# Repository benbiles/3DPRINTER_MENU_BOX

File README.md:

# 3DPRINTER-MENU-BOX

concept: a low cost 3d printer AC fan controller and power switcher for enclosure tempterture regulation and saftey power shutdown 

mainboard uses ESP32 DevKit V1 with Arduino code
screen menu with 4 tactile buttons
1 x OLED screen
2 x DS18B20 Temp sensor channels
2 channels Variable AC 110v / 240v for fan speed control
2 channels 110V / 240V AC solid state relay SSR for shutdown on timer or over temp safety shutdown.

future Mobile APP alarm / notifications / warnings using MIT app inventor.

https://hackaday.io/project/190382-3dprinter-menu-box

current status:
basic menu , oled screen and button with debounce are working.
1 channel temp sensor is working

testing to do soon..
AC fan controller boards and enclosure temp regulation.
extracting the air cools the enclosure too much ?
install a heppa filter and recycle air back into enclosure with fan 1 and extract air with other
when enclosure becomes over temptetur with fan 2 ? 
test power shutdown in case of over temp.

to do later..
install smoke detector for emergency power down.
web cam image minitoring even if just stills taken at intervals.

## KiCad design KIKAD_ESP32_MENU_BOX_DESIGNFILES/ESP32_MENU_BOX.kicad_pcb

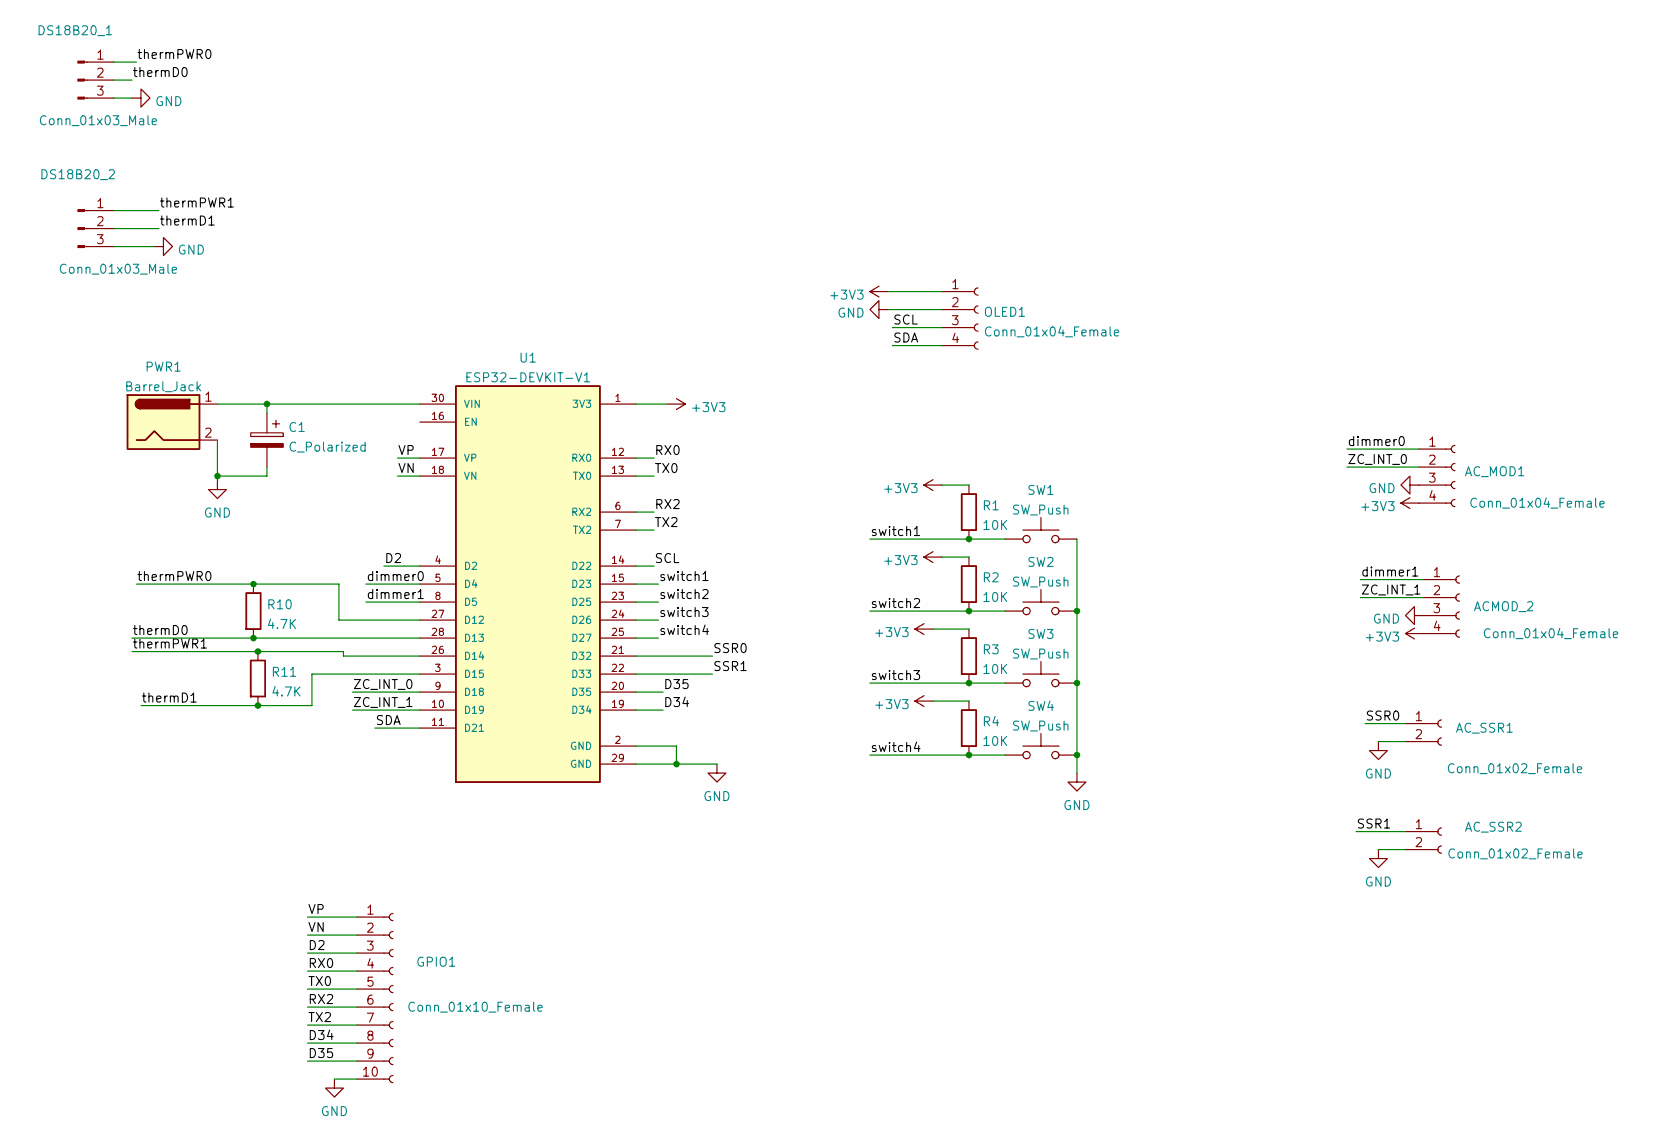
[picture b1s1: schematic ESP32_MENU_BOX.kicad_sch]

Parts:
ACMOD_2: Conn_01x04_Female; PinSocket_1x04_P2.54mm_Vertical
AC_MOD1: Conn_01x04_Female; PinSocket_1x04_P2.54mm_Vertical
AC_SSR1, AC_SSR2: Conn_01x02_Female; PinSocket_1x02_P2.54mm_Vertical
C1: C_Polarized; CP_Elec_8x5.4
DS18B20_1, DS18B20_2: Conn_01x03_Male; PinHeader_1x03_P2.54mm_Vertical
GPIO1: Conn_01x10_Female; PinSocket_1x10_P2.54mm_Vertical
OLED1: Conn_01x04_Female; PinHeader_1x04_P2.54mm_Vertical
PWR1: Barrel_Jack; BarrelJack_GCT_DCJ200-10-A_Horizontal
R1, R2, R3, R4: 10K; R_0603_1608Metric_Pad0.98x0.95mm_HandSolder
R10, R11: 4.7K; R_0603_1608Metric_Pad0.98x0.95mm_HandSolder
SW1, SW2, SW3, SW4: SW_Push; SW_SPST_EVQP2
U1: ESP32-DEVKIT-V1; MODULE_ESP32_DEVKIT_V1; PARTREV N/A

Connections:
+3V3: ACMOD_2.4, AC_MOD1.4, OLED1.1, R1.1, R2.1, R3.1, R4.1, U1.1 (3V3)
/D2: GPIO1.3, U1.4 (D2)
/D34: GPIO1.8, U1.19 (D34)
/D35: GPIO1.9, U1.20 (D35)
/RX0: GPIO1.4, U1.12 (RX0)
/RX2: GPIO1.6, U1.6 (RX2)
/SCL: OLED1.3, U1.14 (D22)
/SDA: OLED1.4, U1.11 (D21)
/SSR0: AC_SSR1.1, U1.21 (D32)
/SSR1: AC_SSR2.1, U1.22 (D33)
/TX0: GPIO1.5, U1.13 (TX0)
/TX2: GPIO1.7, U1.7 (TX2)
/VN: GPIO1.2, U1.18 (VN)
/VP: GPIO1.1, U1.17 (VP)
/ZC_INT_0: AC_MOD1.2, U1.9 (D18)
/ZC_INT_1: ACMOD_2.2, U1.10 (D19)
/dimmer0: AC_MOD1.1, U1.5 (D4)
/dimmer1: ACMOD_2.1, U1.8 (D5)
/switch1: R1.2, SW1.1, U1.15 (D23)
/switch2: R2.2, SW2.1, U1.23 (D25)
/switch3: R3.2, SW3.1, U1.24 (D26)
/switch4: R4.2, SW4.1, U1.25 (D27)
/thermD0: DS18B20_1.2, R10.2, U1.28 (D13)
/thermD1: DS18B20_2.2, R11.2, U1.3 (D15)
/thermPWR0: DS18B20_1.1, R10.1, U1.27 (D12)
/thermPWR1: DS18B20_2.1, R11.1, U1.26 (D14)
GND: ACMOD_2.3, AC_MOD1.3, AC_SSR1.2, AC_SSR2.2, C1.2, DS18B20_1.3, DS18B20_2.3, GPIO1.10, OLED1.2, PWR1.2, SW1.2, SW2.2, SW3.2, SW4.2, U1.2 (GND), U1.29 (GND)
unnamed: C1.1, PWR1.1, U1.30 (VIN)

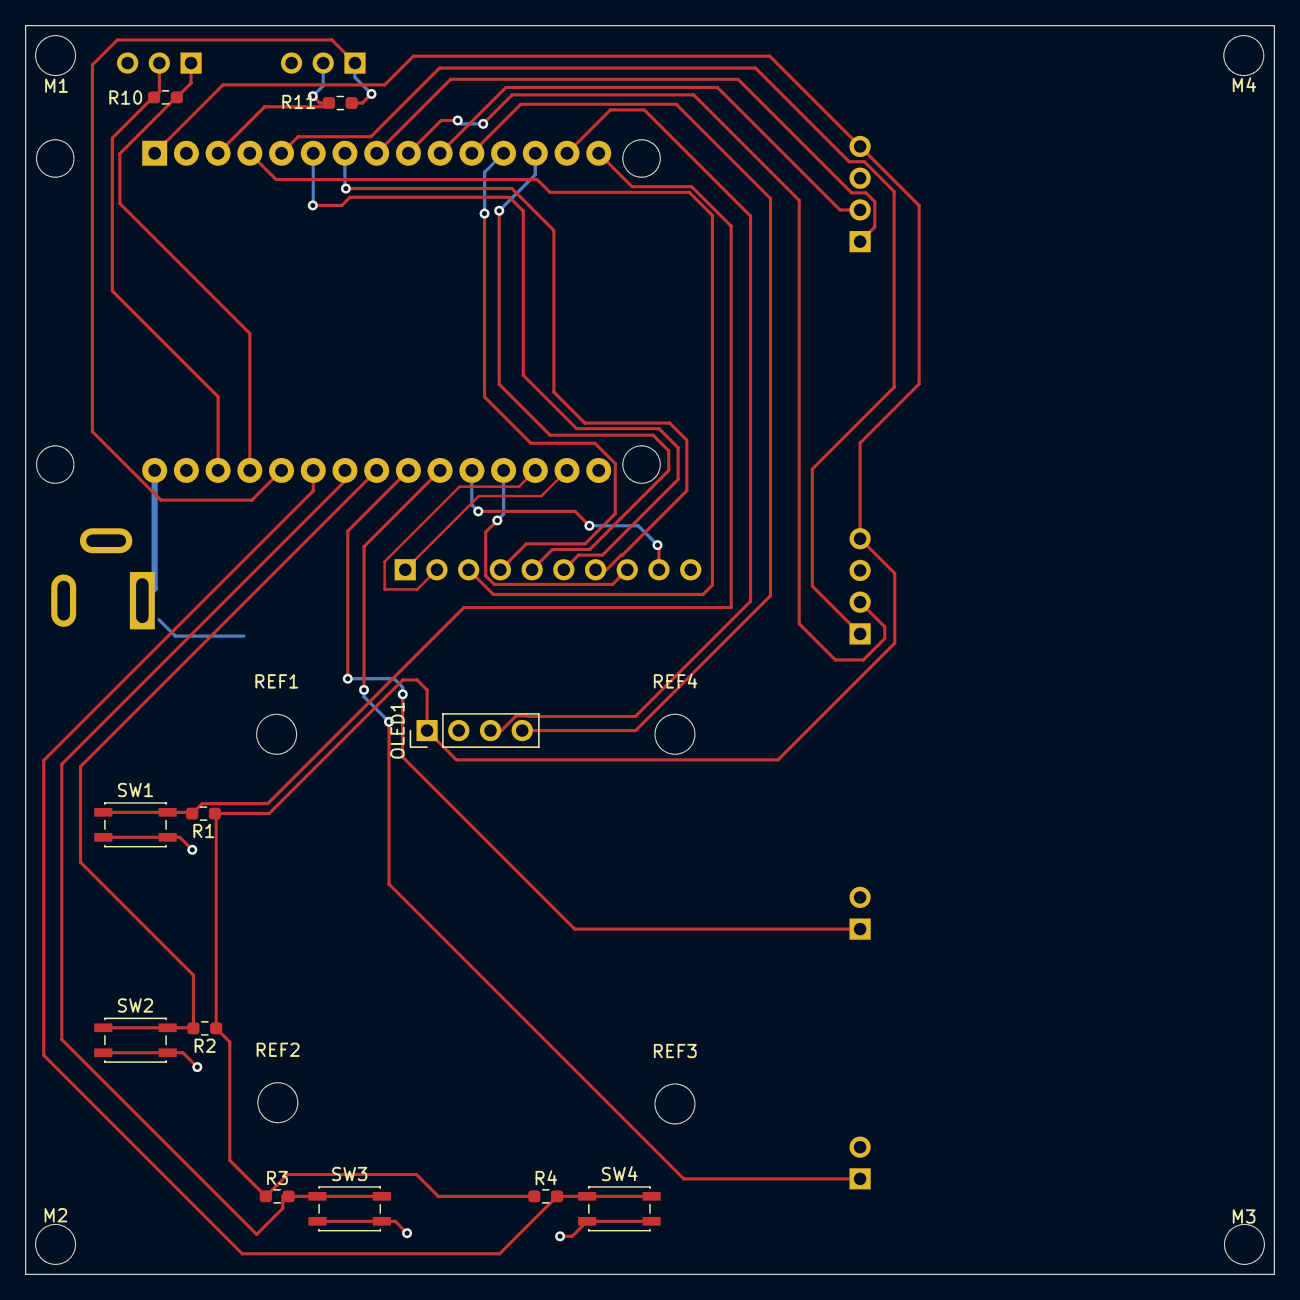
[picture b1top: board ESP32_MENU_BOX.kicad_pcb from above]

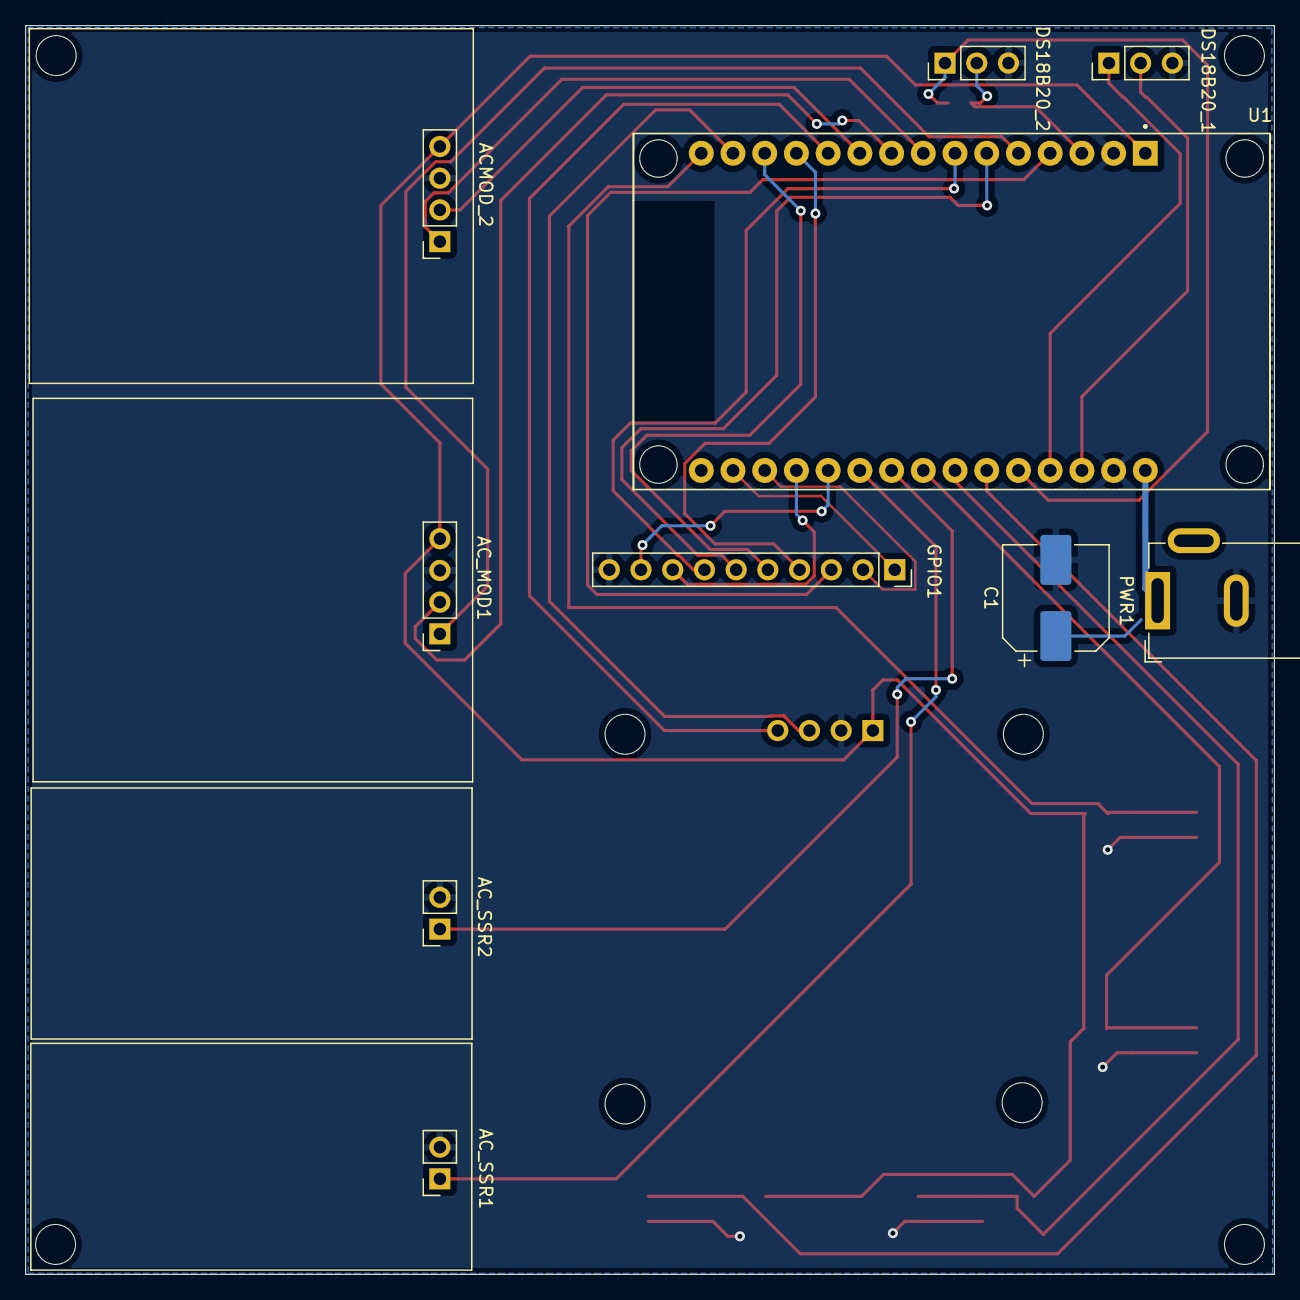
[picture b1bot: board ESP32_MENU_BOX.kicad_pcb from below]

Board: 2 copper layers, 100.0 x 100.0 mm, 29 parts (10 on the bottom side), 28 nets.

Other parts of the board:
M1, M2, M3, M4: MountingHole_3.2mm_M3
REF1, REF2, REF3, REF4: MountingHole_3.2mm_M3

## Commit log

2023-04-18 1st commit
    INITAL COMMIT
2023-04-18 Create Radme
